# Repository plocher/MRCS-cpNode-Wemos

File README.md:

# MRCS-cpNode-Wemos
## License: Creative Commons Attribution-NonCommercial-ShareAlike

cpNode (2.7" Tyco Rail) processor for MRCS CMRI applications

Designed for MRCS as an outgrowth of the [Core-Wemos](/pages/Core-Wemos.html) project, this version includes
CMRI-Net interface circuitry (V4) or interconnect to an external driver (V5 - [CMRI-Bus-Interface](/pages/CMRI-Bus-Interface.html)).

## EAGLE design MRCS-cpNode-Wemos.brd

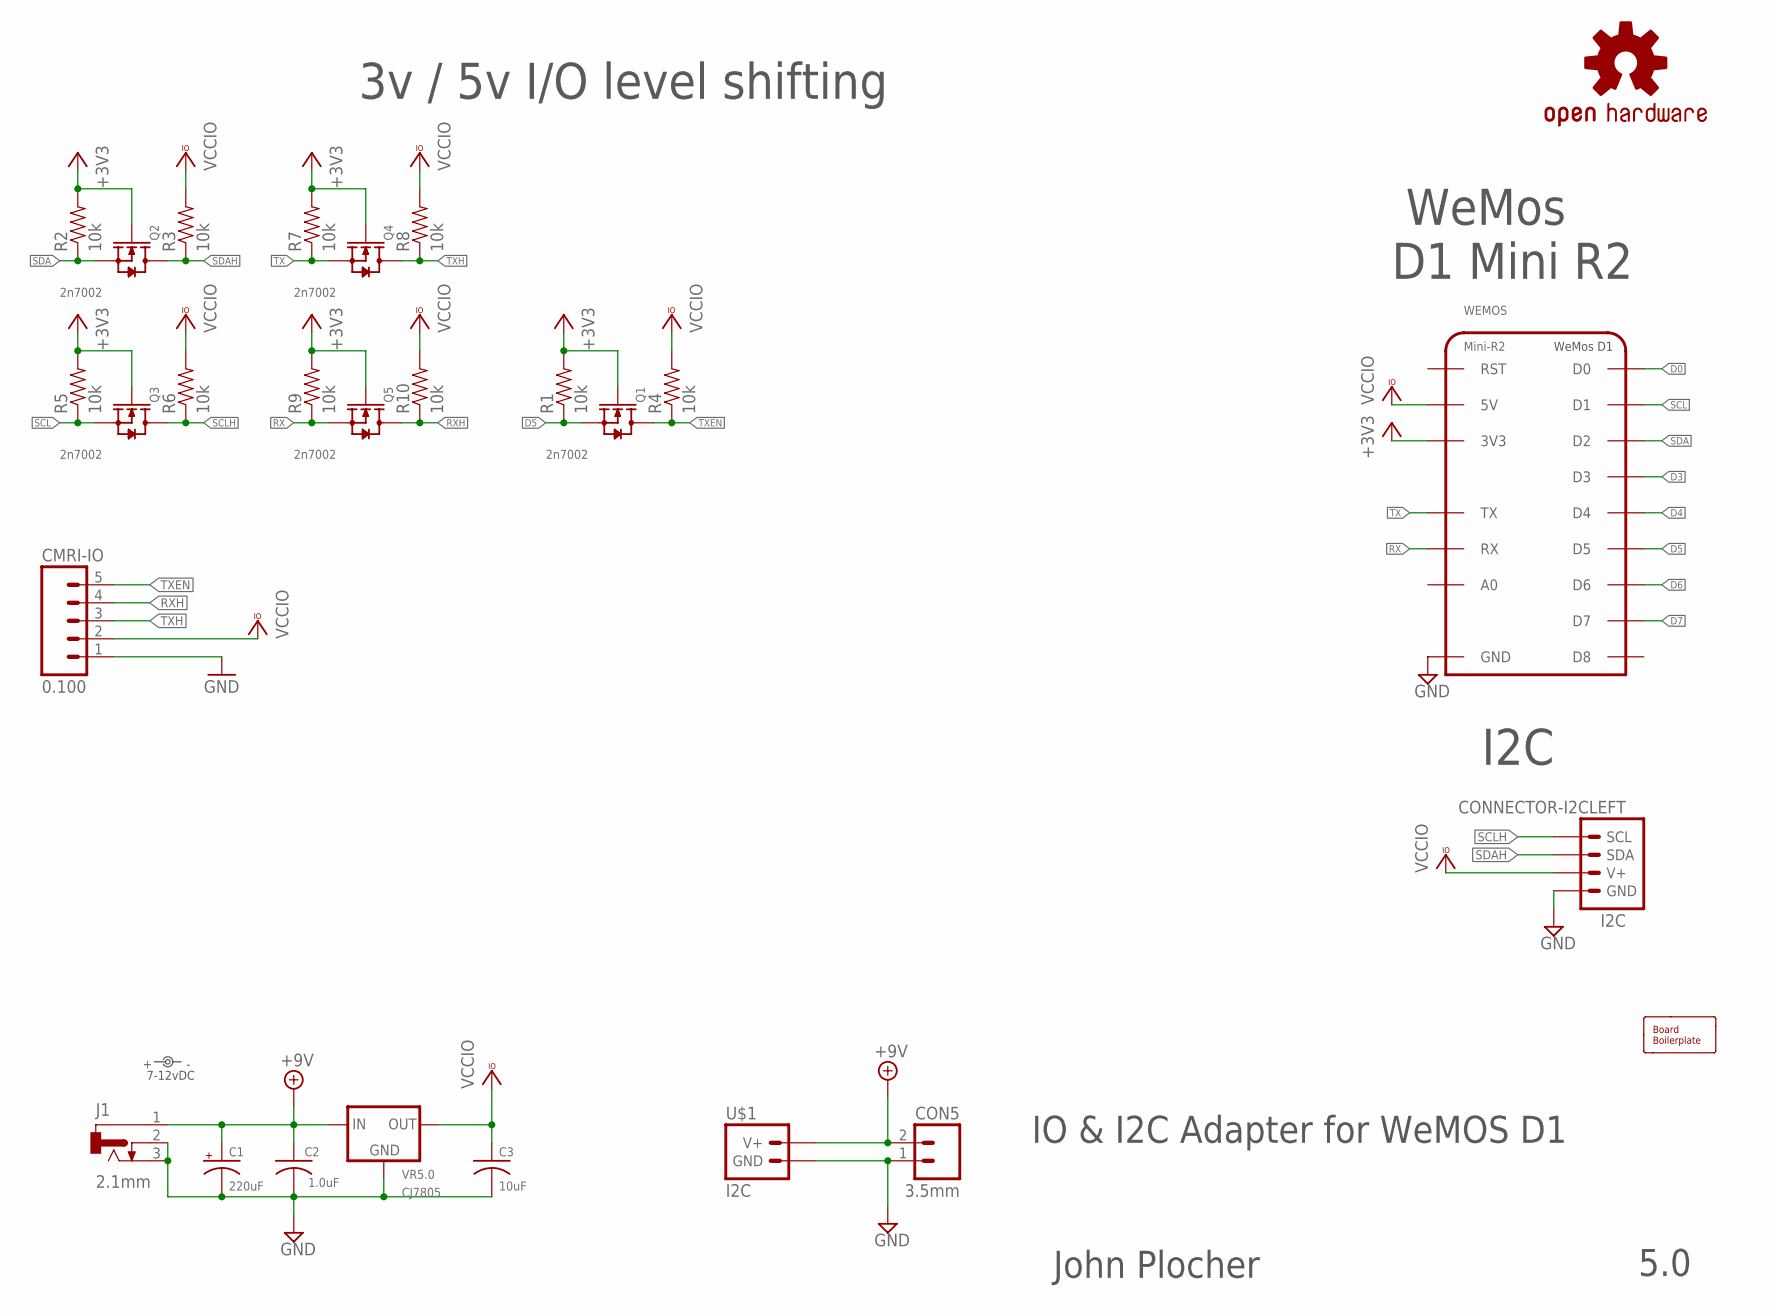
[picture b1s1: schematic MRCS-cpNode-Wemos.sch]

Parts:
BOARD: BOARD; BOARD-DINRAIL-2.7IN-8CM
C1: 220uF; 0810-CAP
C2: 1.0uF; 0603-CAP
C3: 10uF; 0603-CAP
CMRI-IO: 0.100; 1X05_LOCK_LONGPADS
CON5: 3.5mm; SCREWTERMINAL-3.5MM-2_LOCK
I2C: CONNECTOR-I2CLEFT; I2C-L
J1: 2.1mm; DCJ0202
LABEL1: 7-12vDC; PWR_LABEL
OSHW1: OSHW; OSHW-LOGO-L
Q1, Q2, Q3, Q4, Q5: 2n7002; SOT23
R1: 10k; 0805-RES
R2, R3, R4, R5, R6, R7, R8, R9, R10: 10k; 0603-RES
U$1: I2C; POWER-R2
VR5.0: CJ7805; TO-252
WEMOS: Mini-R2; WEMOS-D1

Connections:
+3V3: Q1.1 (G), Q2.1 (G), Q3.1 (G), Q4.1 (G), Q5.1 (G), R1.2, R2.2, R5.2, R7.2, R9.2, WEMOS.3V3
+9V: C1.+, C2.1, CON5.2 (B), J1.1, U$1.V+, U$1.V+@1 (V+), U$1.V+@2 (V+), U$1.V+@3 (V+), VR5.0.1 (IN)
D0: WEMOS.D0
D3: WEMOS.D3
D4: WEMOS.D4
D5: Q1.2 (S), R1.1, WEMOS.D5
D6: WEMOS.D6
D7: WEMOS.D7
GND: C1.-, C2.2, C3.2, CMRI-IO.1, CON5.1 (A), I2C.GND, I2C.GND@1 (GND), J1.2, J1.3, U$1.GND, U$1.GND@1 (GND), U$1.GND@2 (GND), U$1.GND@3 (GND), VR5.0.2 (GND), WEMOS.GND
RX: Q5.2 (S), R9.1, WEMOS.RX
RXH: CMRI-IO.4, Q5.3 (D), R10.1
SCL: Q3.2 (S), R5.1, WEMOS.D1
SCLH: I2C.SCL, I2C.SCL@1 (SCL), Q3.3 (D), R6.1
SDA: Q2.2 (S), R2.1, WEMOS.D2
SDAH: I2C.SDA, I2C.SDA@1 (SDA), Q2.3 (D), R3.1
TX: Q4.2 (S), R7.1, WEMOS.TX
TXEN: CMRI-IO.5, Q1.3 (D), R4.1
TXH: CMRI-IO.3, Q4.3 (D), R8.1
VCCIO: C3.1, CMRI-IO.2, I2C.V+, I2C.V+@1 (V+), R3.2, R4.2, R6.2, R8.2, R10.2, VR5.0.3 (OUT), WEMOS.5V

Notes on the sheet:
IO & I2C Adapter for WeMOS D1
John Plocher
5.0
I2C
WeMos D1 Mini R2
3v / 5v I/O level shifting

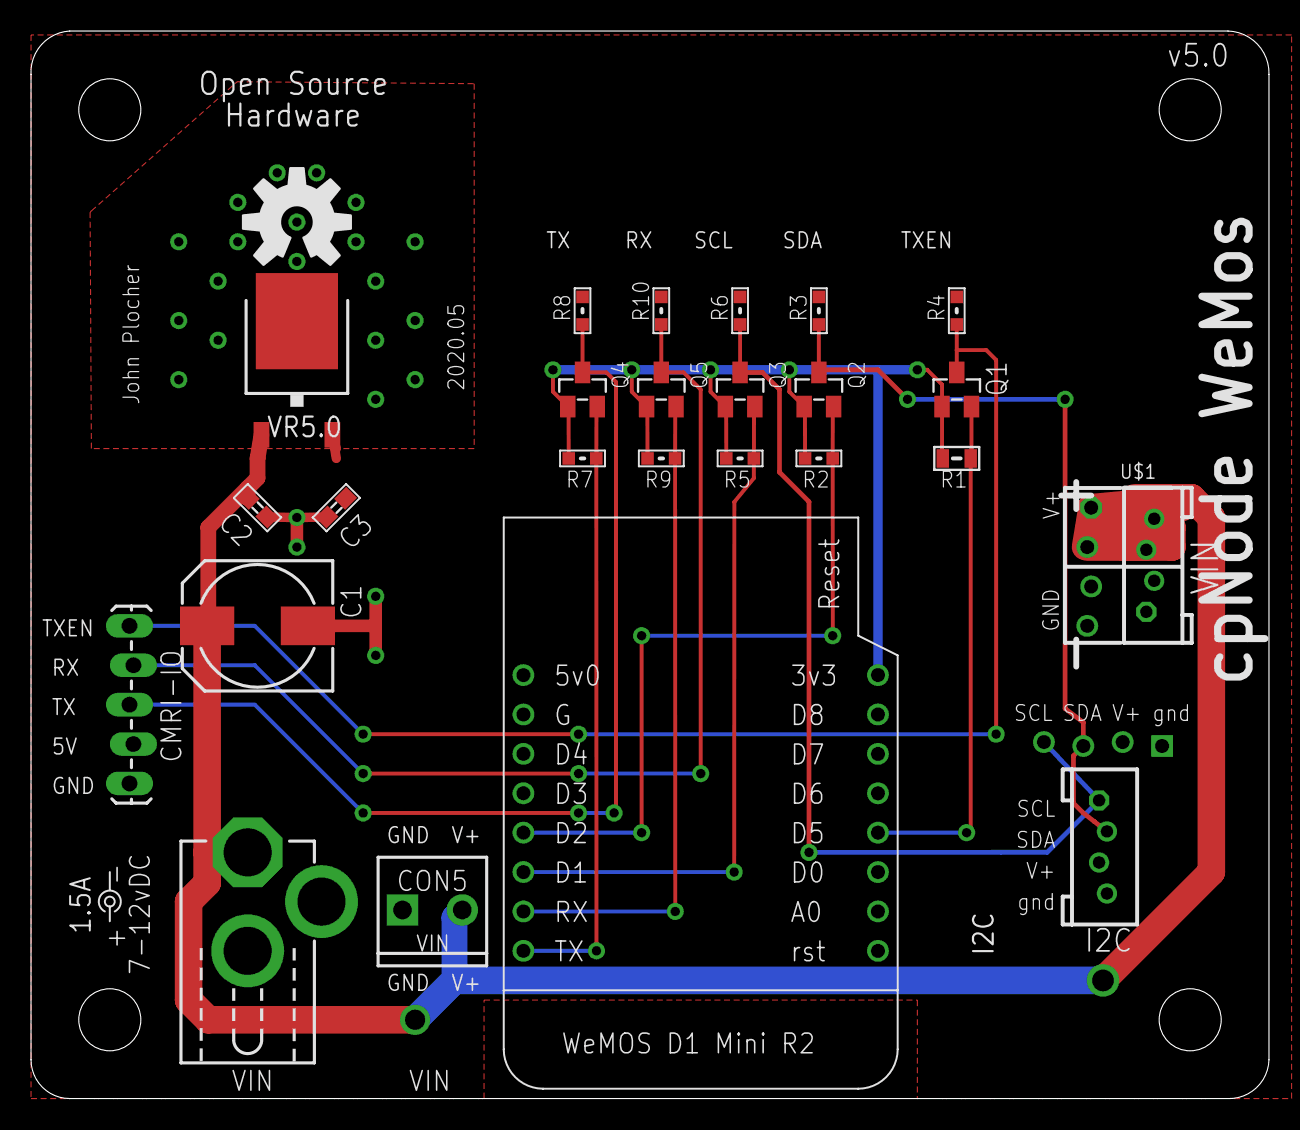
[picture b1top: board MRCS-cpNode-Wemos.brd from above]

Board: 2 copper layers, 79.8 x 68.8 mm, 28 parts (0 on the bottom side), 14 nets.

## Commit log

2019-11-28 ensured License is CC-NC-SA
2020-05-04 updated tags
2020-05-05 cleanup, DRC, ERC
2020-10-05 added missing values
2020-10-06 normalized values
